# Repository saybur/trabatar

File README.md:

trabatar
========

A simple Java program to share a modern computer's keyboard and mouse with a
classic Mac over an ADB connection. This lets you control your old Mac
sitting next to your main computer without keeping two sets of input
devices around.

The hardware required for this connection is
[trabular](https://github.com/saybur/trabular).  Please see that project
for information about what you need to create to make this work.

This software is written in Java, and should build and run on any platform with
JavaSE 1.8 or newer. The excellent [jSerialComm](https://fazecast.github.io/jSerialComm/)
library is used to provide cross-platform serial port access to the hardware.

This is in an early stage of development and will change significantly.
More documentation will be added soon.  Any feedback is appreciated.

License
-------

Except where otherwise noted, all files in this repository are available under
the terms of the GNU General Public License, version 3, available in the
LICENSE document. There is NO WARRANTY, not even for MERCHANTABILITY or
FITNESS FOR A PARTICULAR PURPOSE. For details, refer to the license.

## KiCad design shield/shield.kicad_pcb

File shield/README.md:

trabatar-shield
===============

**IMPORTANT WARNING: THIS HARDWARE IS UNTESTED!**

A very simple shield for [Arduino Nano](https://store.arduino.cc/usa/arduino-nano)
providing an [Apple Desktop Bus](https://en.wikipedia.org/wiki/Apple_Desktop_Bus)
connection. This allows software running on the Arduino (or a connected
computer) to communicate across ADB with a retro computer or peripherals.

Components
----------

The goal of this hardware is a simple, very easy-to-assemble board. The
following components are needed.

* 1x TE 5749181-1 4-pin Mini-DIN connector
* 2x 2N3904 transistors
* 3x 4.7Kohm resistors
* 1x 100Kohm resistor
* 2x 15-pin 100mil female headers

One 4.7Kohm resistor (R2) is used to help pull-up the ADB data line to 5V,
along with the resistor in the ADB host. Another 4.7Kohm resistor (R1) is used
to limit the current through the base of of the transistor (Q1) for asserting
the ADB data line, and the final 4.7Kohm resistor (R3) is used in the same
fashion for the transistor (Q2) on the ADB power line. The 100Kohm resistor
(R4) helps bias the data line low to prevent the bus floating when remote
device(s) are off or disconnected. These specific resistor values are not
critical and similar values would likely work fine, but have not been tested.

The transistors may also be replaced with other TO-96 / TO-226 bipolar NPN
transistors having the same pinout and similiar characteristics, particularly
the ability to come out of saturation within a few microseconds. Potential
examples include the PN2222, though that part is untested.

Limitations
-----------

The simplicity of this board means there are a number of things to be aware of
when using it.

* No electrostatic discharge protection is present apart from what is offered
  by the AVR microcontroller.
* There is no protection against [latch-up](https://en.wikipedia.org/wiki/Latch-up)
  caused by the ADB host starting before the Arduino board. Users must ensure
  the board is powered before any ADB device(s).
* If the USB 5V rail is 0.05 volts or lower relative to ADB 5V, the circuit may
  violate the V<sub>IH</sub> rating of the AVR due to the forward voltage drop
  of the USB rectifier diode.
* There is a common ground between the Arduino and connected ADB devices, as
  well as any connected USB host.

There are likely other caveats the author is unaware of. User contributions are
welcome, both in knowledge and design.

License
-------

These files are available under the terms of the GNU General Public License,
version 3, available in the LICENSE document in the parent directory. There is
NO WARRANTY, not even for MERCHANTABILITY or FITNESS FOR A PARTICULAR PURPOSE.
For details, refer to the license.

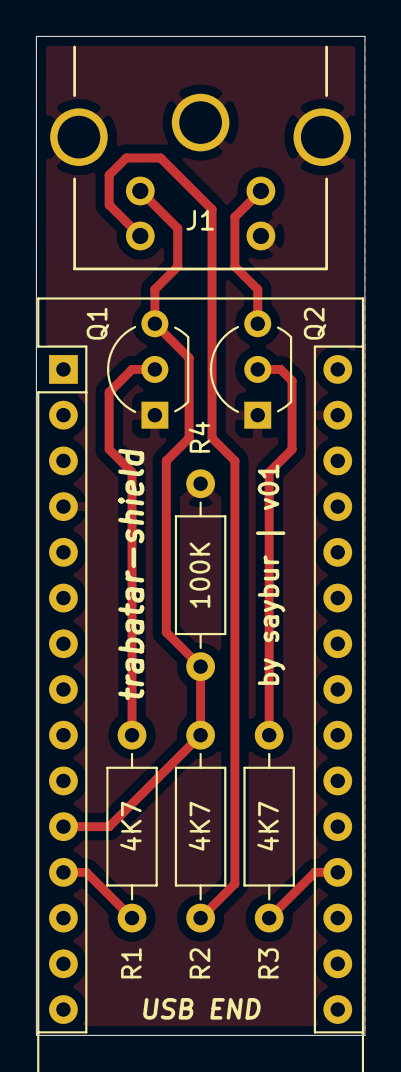
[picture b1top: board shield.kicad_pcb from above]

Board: 2 copper layers, 18.2 x 55.5 mm, 8 parts (0 on the bottom side), 8 nets.

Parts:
A1: Arduino_Nano_v3.x; Arduino_Nano
J1: Mini-DIN-4; 5749181-1
Q1, Q2: 2N3904; TO-92_Inline_Wide
R1, R2, R3: 4K7; R_Axial_DIN0207_L6.3mm_D2.5mm_P10.16mm_Horizontal
R4: 100K; R_Axial_DIN0207_L6.3mm_D2.5mm_P10.16mm_Horizontal

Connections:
GND: A1.4, A1.29, J1.4, Q1.1, Q2.1, R4.1
unnamed: A1.11, J1.1, Q1.3, R2.1, R4.2
unnamed: A1.12, R1.2
unnamed: A1.19, R3.2
unnamed: J1.2, Q2.3
unnamed: J1.3, R2.2
unnamed: Q1.2, R1.1
unnamed: Q2.2, R3.1

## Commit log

2016-10-31 Initial work.
2016-10-31 Added junit to dependencies for testing
2016-10-31 Tweaks to how the final .jar is produced
2016-10-31 Disallow resizing of window
2016-10-31 Attempt at trying to fix bad mouse drag behavior
2021-07-10 Purge Eclipse files from repo.
2021-07-10 Updates to .gitignore, for Eclipse and unused J2ME stuff.
2021-07-10 Re-formatted and added 1.8 compliance.
2021-07-10 Switch to slf4j-api
2021-07-10 main() moved into primary class.
2021-07-10 No longer report destination in title bar.
2021-07-10 Initial switch to using jSerialComm.
2021-07-10 Release via the right control key, not 5x shift.
2021-07-10 Reformat, add license reminder.
2021-07-10 Nano shield, revision 1.
2021-07-10 Note switch to cross-platform serial library.
2021-07-17 Added "send" menu for interrupt/reset combinations.
    This is glitchy with the transmit interface, but that will need to be fixed later.
2021-07-17 Added numpad '.' button support.
2021-07-17 Try to chill the mouse out a bit.
    Need a better algorithm for this. You basically have two acceleration algorithms going, one on the host and the other on the Mac (unless it is set to "very slow").
